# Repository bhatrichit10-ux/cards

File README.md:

# cards
my own very little pcb cards <br>
They are built from scratch and use very simple core logics
## PCB
 <br>
 <br>
## Schematic
 <br>

## Firmware
Made with CircuitPython using Adafruit's NeoPixel library <br>

## BOM
|serial|item           |cost/p|count|total/item|link            |
|------|---------------|------|-----|----------|----------------|
|1     |PCB            |$10   |1    |$10       |lioncircuits.com|
|2     |XIAO RP2040 DIP|0     |0    |0         | i alr these    |
|3     |SK6812MINI-E   |0     |0    |0         |i alr have these|

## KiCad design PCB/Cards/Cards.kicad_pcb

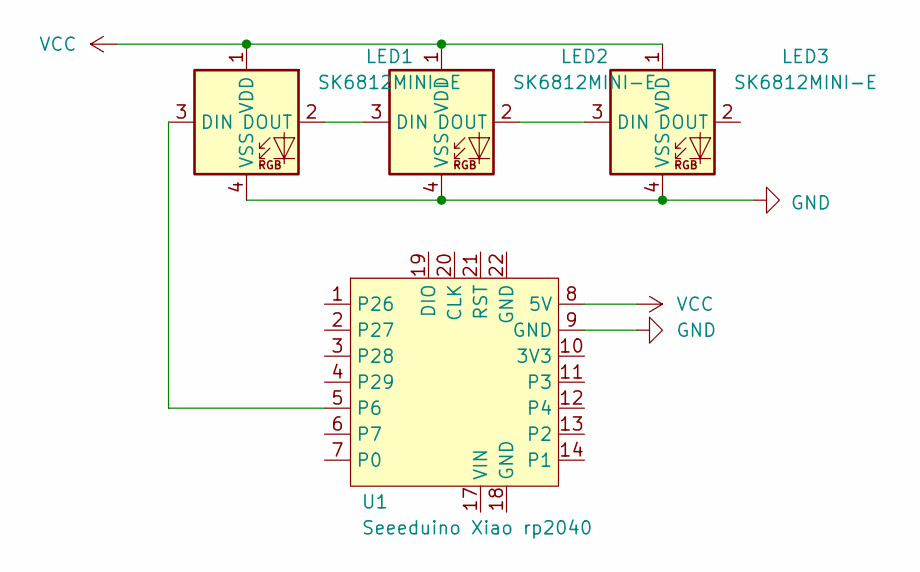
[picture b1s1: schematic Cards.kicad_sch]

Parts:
LED1, LED2, LED3: SK6812MINI-E; LED_6028R
U1: Seeeduino Xiao rp2040; Xiao_rp2040_ACH

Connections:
GND: LED1.4 (VSS), LED2.4 (VSS), LED3.4 (VSS), U1.9 (GND)
unnamed: LED1.3 (DIN), U1.5 (P6)
unnamed: LED1.2 (DOUT), LED2.3 (DIN)
unnamed: LED2.2 (DOUT), LED3.3 (DIN)
VCC: LED1.1 (VDD), LED2.1 (VDD), LED3.1 (VDD), U1.8 (5V)

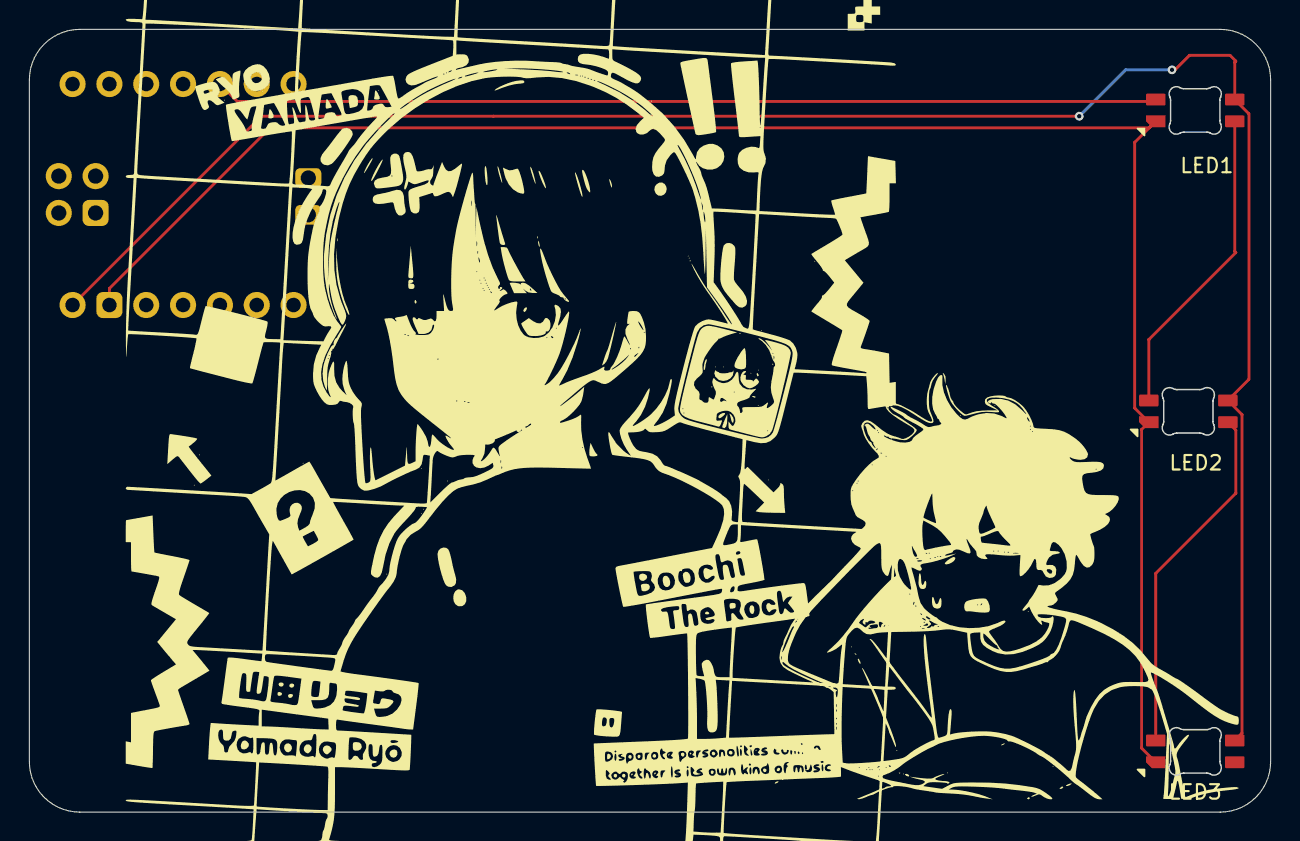
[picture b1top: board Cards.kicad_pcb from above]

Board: 2 copper layers, 85.5 x 53.9 mm, 4 parts (1 on the bottom side), 5 nets.

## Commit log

2026-05-12 Ship it
2026-06-19 Update README with new images and formatting
    Added additional images and HTML line breaks for formatting.
2026-06-19 Revise description in README.md
    Updated the description of the PCB cards section.
